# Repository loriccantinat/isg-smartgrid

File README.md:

À propos
========

Ce projet contient les ressources de base pour le projet ISG.

Il contient notamment toutes les informations à propos de la carte MPPTv2
prototype utilisée dans ce projet.

License
=======

À l'exception du dossier datasheets, e projet est partagé sous la licence libre
*Creative Commons Attribution-ShareAlike 4.0 International Public License*.

Pour plus d'informations, voir le fichier `COPYING`.

Les datasheets sont la propriétés des différents fabricants et ont été recopiées
ici pour des raison pratique.

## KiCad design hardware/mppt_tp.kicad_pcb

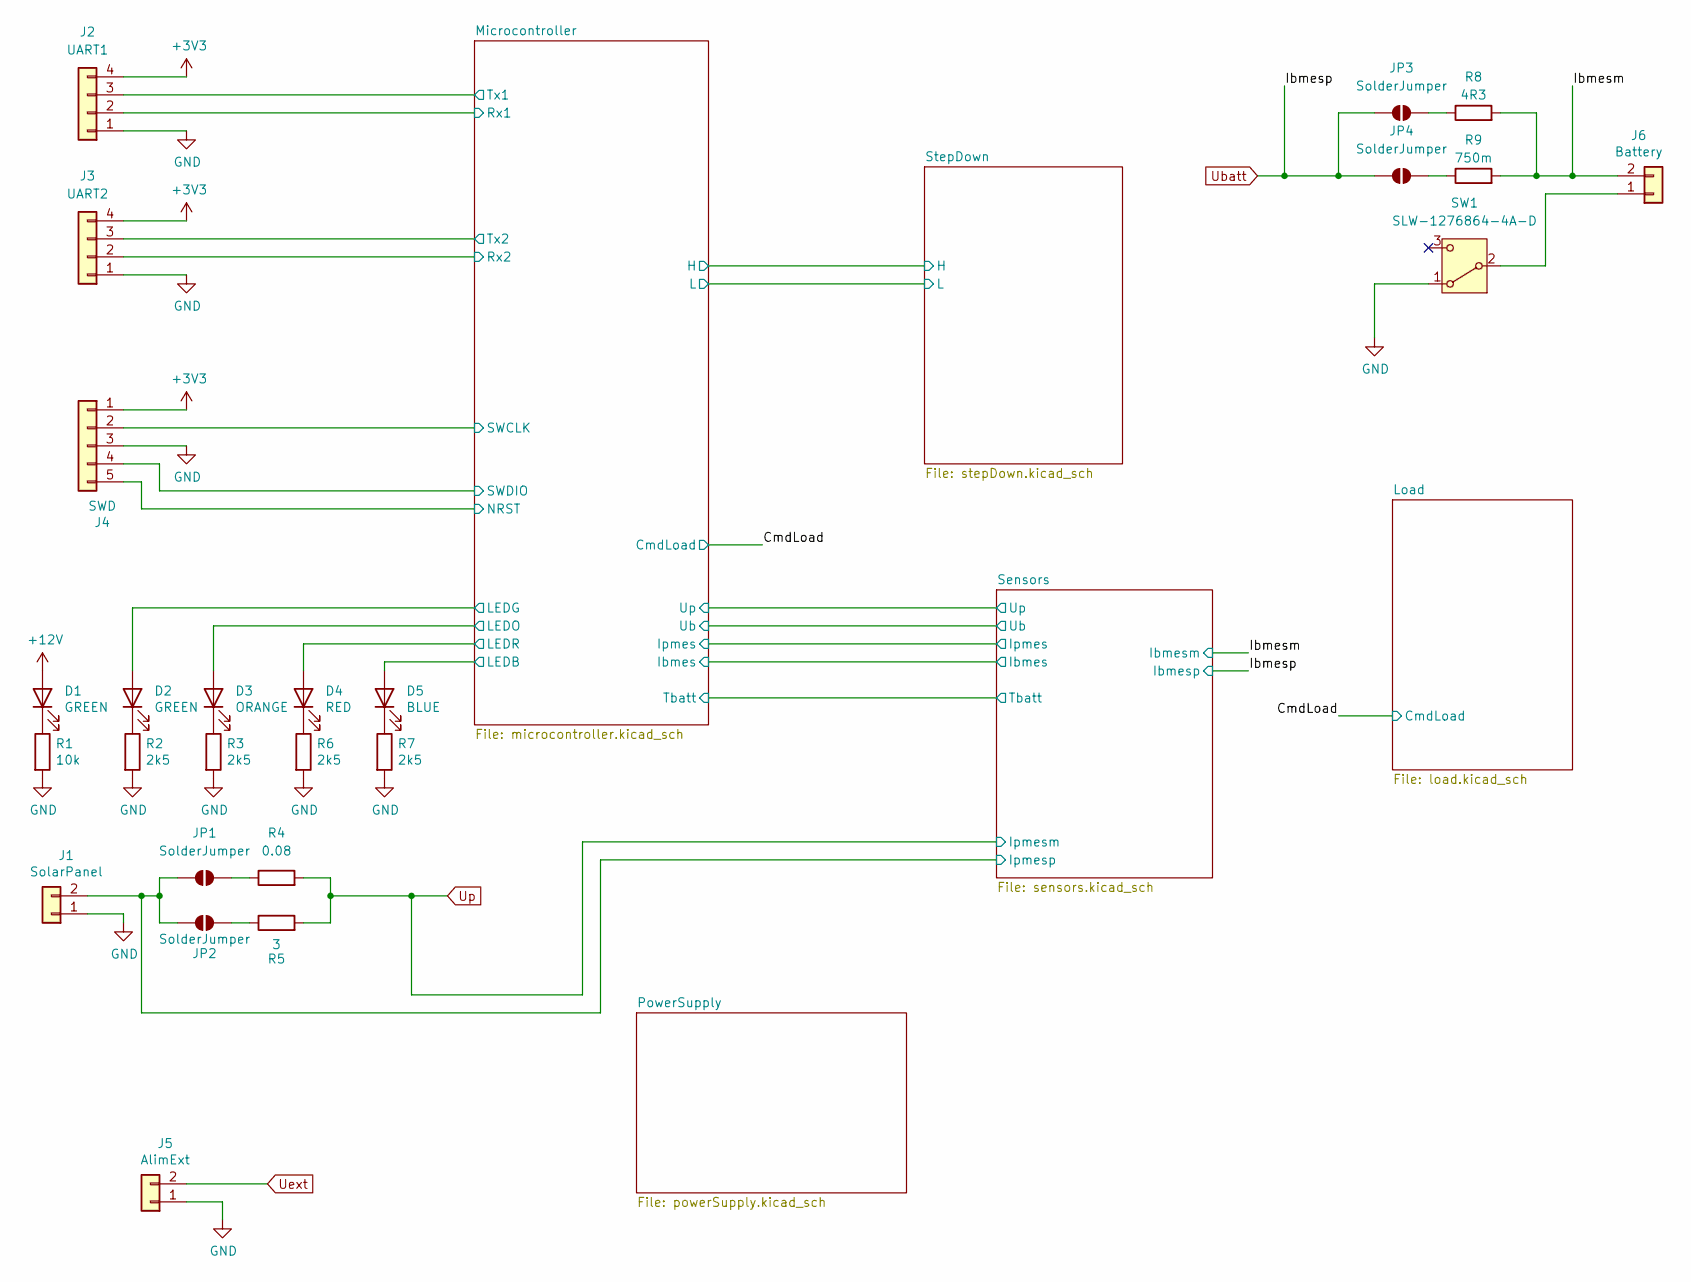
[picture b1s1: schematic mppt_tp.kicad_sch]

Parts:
D1, D2: GREEN; LED_150141_Wurth_HandSolder
D3: ORANGE; LED_150141_Wurth_HandSolder
D4: RED; LED_150141_Wurth_HandSolder
D5: BLUE; LED_150141_Wurth_HandSolder
J1: SolarPanel; Molex_KK-254_AE-6410-02A_1x02_P2.54mm_Vertical
J2: UART1; Molex_KK-254_AE-6410-04A_1x04_P2.54mm_Vertical
J3: UART2; Molex_KK-254_AE-6410-04A_1x04_P2.54mm_Vertical
J4: SWD; Molex_KK-254_AE-6410-05A_1x05_P2.54mm_Vertical
J5: AlimExt; Molex_KK-254_AE-6410-02A_1x02_P2.54mm_Vertical
J6: Battery; Molex_KK-254_AE-6410-02A_1x02_P2.54mm_Vertical
JP1, JP2, JP3, JP4: SolderJumper; SolderJumper-2_P1.3mm_Open_TrianglePad1.0x1.5mm
R1: 10k; R_0805_2012Metric_Pad1.20x1.40mm_HandSolder
R2, R3, R6, R7: 2k5; R_0805_2012Metric_Pad1.20x1.40mm_HandSolder
R4: 0.08; R_1206_3216Metric_HandSolder
R5: 3; R_1206_3216Metric_HandSolder
R8: 4R3; R_1206_3216Metric_HandSolder
R9: 750m; R_1206_3216Metric_HandSolder
SW1: SLW-1276864-4A-D; Switch_SLW-1276864_THT

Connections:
+3V3: J2.4, J3.4, J4.1; also elsewhere on the board
+12V: D1.2 (A); also elsewhere on the board
/Ibmesm: J6.2, R8.2, R9.2; also elsewhere on the board
/Microcontroller/LEDB: D5.2 (A); also elsewhere on the board
/Microcontroller/LEDG: D2.2 (A); also elsewhere on the board
/Microcontroller/LEDO: D3.2 (A); also elsewhere on the board
/Microcontroller/LEDR: D4.2 (A); also elsewhere on the board
/Microcontroller/NRST: J4.5; also elsewhere on the board
/Microcontroller/Rx1: J2.2; also elsewhere on the board
/Microcontroller/Rx2: J3.2; also elsewhere on the board
/Microcontroller/SWCLK: J4.2; also elsewhere on the board
/Microcontroller/SWDIO: J4.4; also elsewhere on the board
/Microcontroller/Tx1: J2.3; also elsewhere on the board
/Microcontroller/Tx2: J3.3; also elsewhere on the board
/Sensors/Ipmesp: J1.2, JP1.1 (A), JP2.1 (A); also elsewhere on the board
GND: J1.1, J2.1, J3.1, J4.3, J5.1, R1.2, R2.2, R3.2, R6.2, R7.2, SW1.1 (A); also elsewhere on the board
unnamed: D1.1 (K), R1.1
unnamed: D2.1 (K), R2.1
unnamed: D3.1 (K), R3.1
unnamed: D4.1 (K), R6.1
unnamed: D5.1 (K), R7.1
unnamed: J6.1, SW1.2 (B)
unnamed: JP1.2 (B), R4.1
unnamed: JP2.2 (B), R5.1
unnamed: JP3.2 (B), R8.1
unnamed: JP4.2 (B), R9.1
Ubatt: JP3.1 (A), JP4.1 (A); also elsewhere on the board
Uext: J5.2; also elsewhere on the board
Up: R4.2, R5.2; also elsewhere on the board

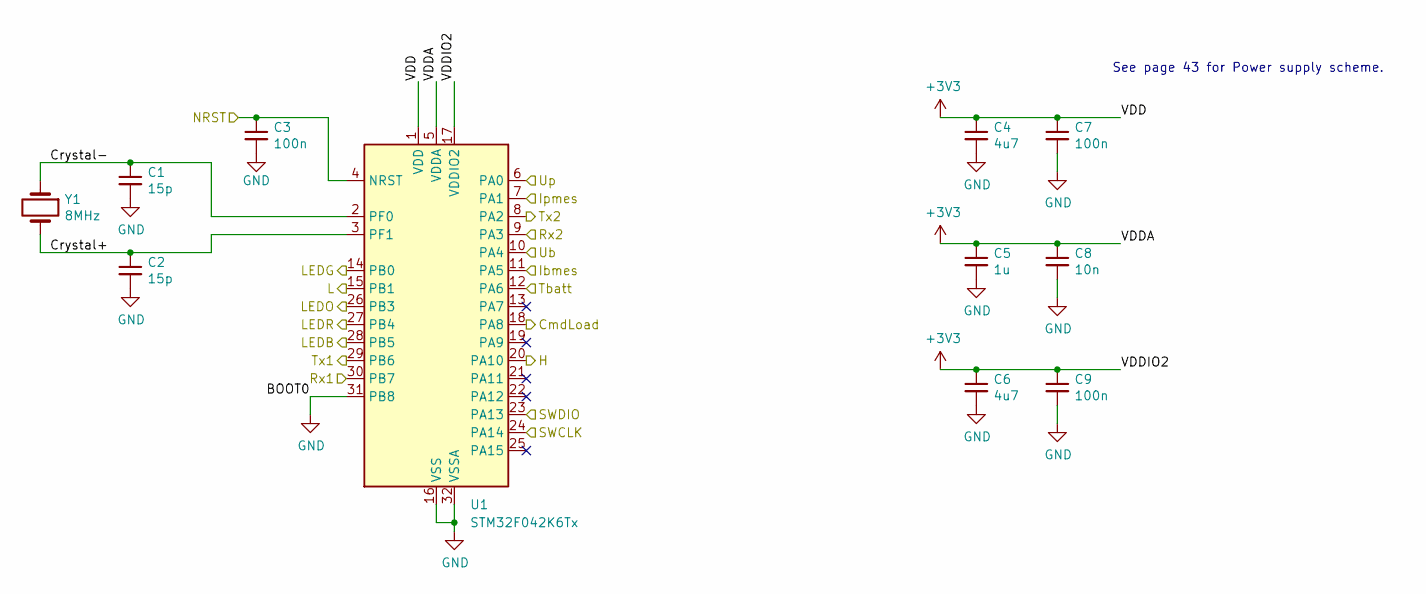
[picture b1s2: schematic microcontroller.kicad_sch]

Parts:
C1, C2: 15p; C_0805_2012Metric_Pad1.18x1.45mm_HandSolder
C3, C7, C9: 100n; C_0805_2012Metric_Pad1.18x1.45mm_HandSolder
C4, C6: 4u7; C_0805_2012Metric_Pad1.18x1.45mm_HandSolder
C5: 1u; C_0805_2012Metric_Pad1.18x1.45mm_HandSolder
C8: 10n; C_0805_2012Metric_Pad1.18x1.45mm_HandSolder
U1: STM32F042K6Tx; LQFP-32_7x7mm_P0.8mm_HandSolder
Y1: 8MHz; Crystal_SMD_ABLS2

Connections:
+3V3: C4.1, C5.1, C6.1, C7.1, C8.1, C9.1, U1.1 (VDD), U1.5 (VDDA), U1.17 (VDDIO2); also elsewhere on the board
/CmdLoad: U1.18 (PA8); also elsewhere on the board
/Microcontroller/Crystal+: C2.1, U1.3 (PF1), Y1.2
/Microcontroller/Crystal-: C1.1, U1.2 (PF0), Y1.1
/Microcontroller/H: U1.20 (PA10); also elsewhere on the board
/Microcontroller/Ibmes: U1.11 (PA5); also elsewhere on the board
/Microcontroller/Ipmes: U1.7 (PA1); also elsewhere on the board
/Microcontroller/L: U1.15 (PB1); also elsewhere on the board
/Microcontroller/LEDB: U1.28 (PB5); also elsewhere on the board
/Microcontroller/LEDG: U1.14 (PB0); also elsewhere on the board
/Microcontroller/LEDO: U1.26 (PB3); also elsewhere on the board
/Microcontroller/LEDR: U1.27 (PB4); also elsewhere on the board
/Microcontroller/NRST: C3.1, U1.4 (NRST); also elsewhere on the board
/Microcontroller/Rx1: U1.30 (PB7); also elsewhere on the board
/Microcontroller/Rx2: U1.9 (PA3); also elsewhere on the board
/Microcontroller/SWCLK: U1.24 (PA14); also elsewhere on the board
/Microcontroller/SWDIO: U1.23 (PA13); also elsewhere on the board
/Microcontroller/Tbatt: U1.12 (PA6); also elsewhere on the board
/Microcontroller/Tx1: U1.29 (PB6); also elsewhere on the board
/Microcontroller/Tx2: U1.8 (PA2); also elsewhere on the board
/Microcontroller/Ub: U1.10 (PA4); also elsewhere on the board
/Microcontroller/Up: U1.6 (PA0); also elsewhere on the board
GND: C1.2, C2.2, C3.2, C4.2, C5.2, C6.2, C7.2, C8.2, C9.2, U1.16 (VSS), U1.31 (PB8), U1.32 (VSSA); also elsewhere on the board

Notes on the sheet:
See page 43 for Power supply scheme.

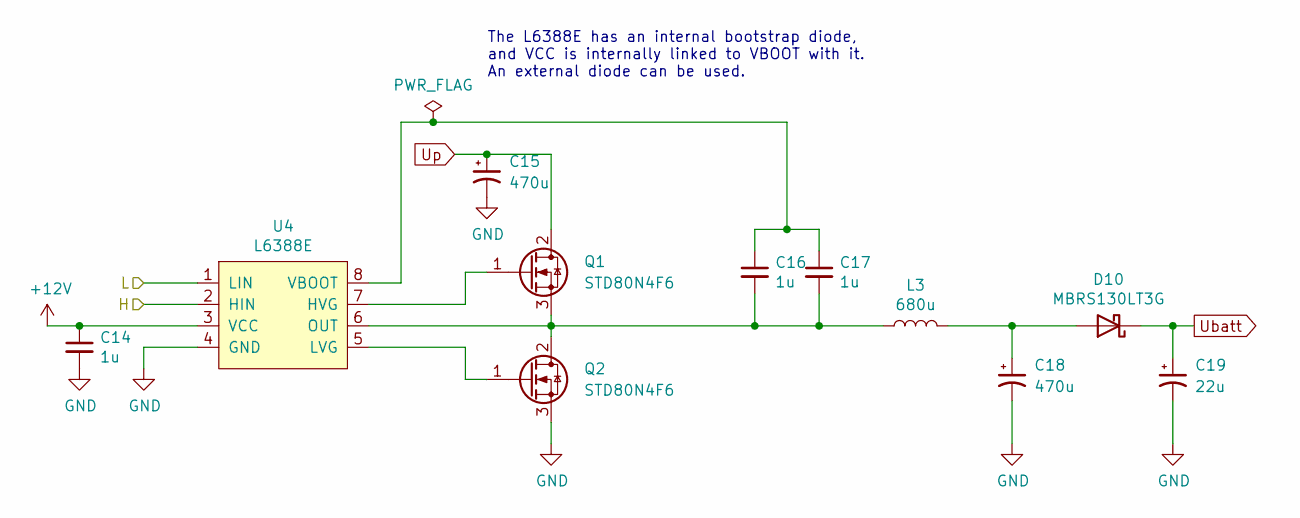
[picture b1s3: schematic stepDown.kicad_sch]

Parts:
C14, C16, C17: 1u; C_0805_2012Metric_Pad1.18x1.45mm_HandSolder
C15, C18: 470u; CP_Elec_16x16.5_Panasonic
C19: 22u; CP_Elec_6.3x5.8_Panasonic_HandSolder
D10: MBRS130LT3G; Diode_SMD_MBRS130LT3G_HandSolder
L3: 680u; Inductor_SMD_Coilcraft_MSS1278H_HandSolder
Q1, Q2: STD80N4F6; TO-252-2_HandSolder
U4: L6388E; SO-8_3.9x4.9mm_P1.27mm_HandSolder

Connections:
+12V: C14.1, U4.3 (VCC); also elsewhere on the board
/Microcontroller/H: U4.2 (HIN); also elsewhere on the board
/Microcontroller/L: U4.1 (LIN); also elsewhere on the board
GND: C14.2, C15.2, C18.2, C19.2, Q2.3 (S), U4.4 (GND); also elsewhere on the board
unnamed: C18.1, D10.2 (A), L3.2
unnamed: Q1.1 (G), U4.7 (HVG)
unnamed: C16.2, C17.2, L3.1, Q1.3 (S), Q2.2 (D), U4.6 (OUT)
unnamed: Q2.1 (G), U4.5 (LVG)
unnamed: C16.1, C17.1, U4.8 (VBOOT)
Ubatt: C19.1, D10.1 (K); also elsewhere on the board
Up: C15.1, Q1.2 (D); also elsewhere on the board

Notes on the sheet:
The L6388E has an internal bootstrap diode, and VCC is internally linked to VBOOT with it. An external diode can be used.

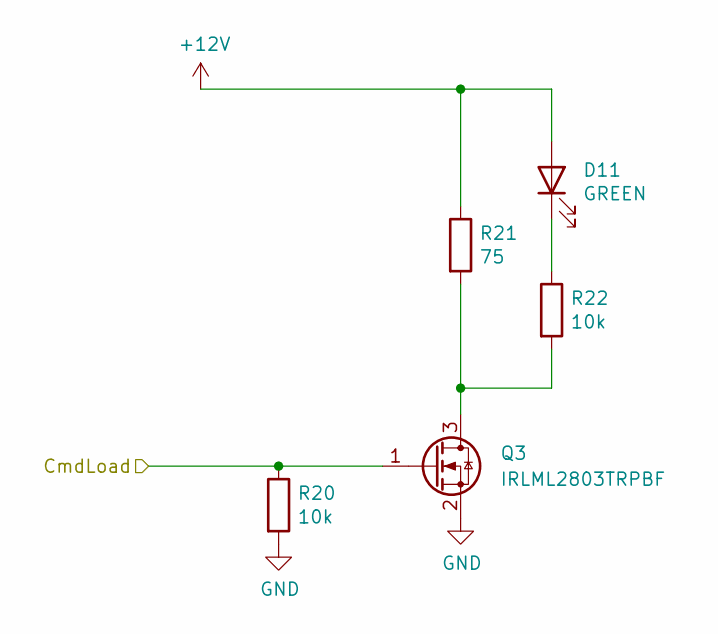
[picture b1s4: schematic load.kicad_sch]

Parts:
D11: GREEN; LED_150141_Wurth_HandSolder
Q3: IRLML2803TRPBF; SOT-23_Handsoldering
R20, R22: 10k; R_0805_2012Metric_Pad1.20x1.40mm_HandSolder
R21: 75; Resistor_SMD_1225Large_HandSolder

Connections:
+12V: D11.2 (A), R21.1; also elsewhere on the board
/CmdLoad: Q3.1 (G), R20.1; also elsewhere on the board
GND: Q3.2 (S), R20.2; also elsewhere on the board
unnamed: D11.1 (K), R22.1
unnamed: Q3.3 (D), R21.2, R22.2

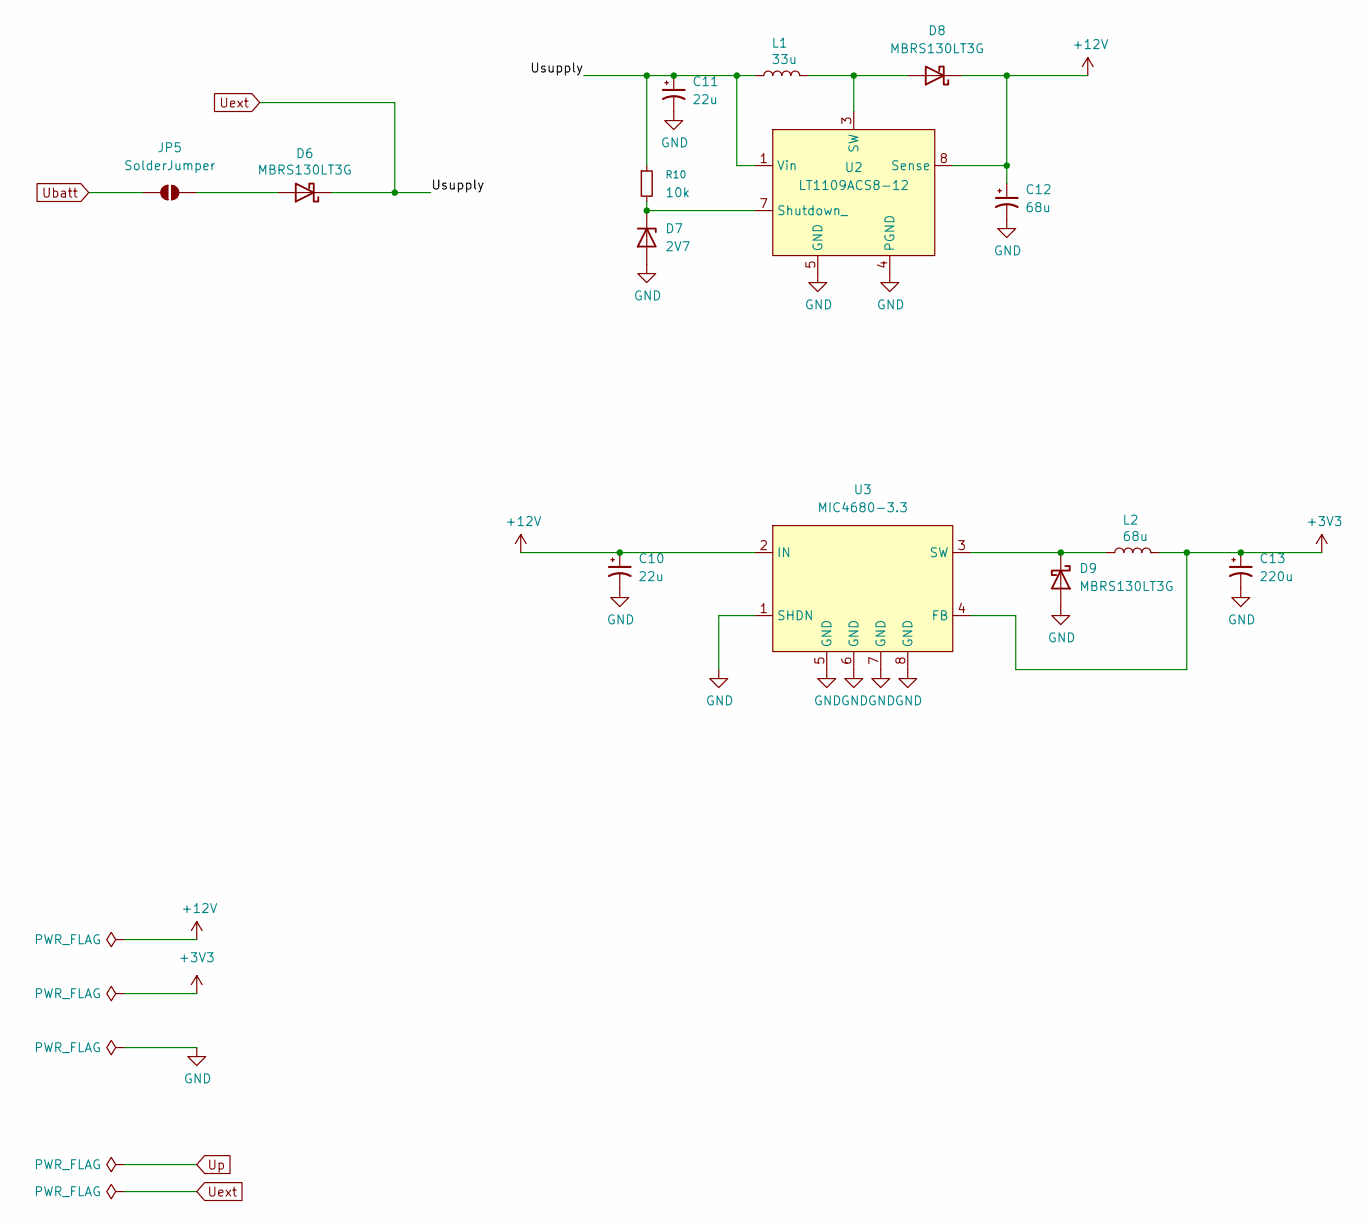
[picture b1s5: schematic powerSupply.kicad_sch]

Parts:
C10, C11: 22u; CP_Elec_6.3x5.8_Panasonic_HandSolder
C12: 68u; CP_Elec_8x10.5_Panasonic_HandSolder
C13: 220u; CP_Elec_10x10.5_Panasonic_HandSolder
D6, D8, D9: MBRS130LT3G; Diode_SMD_MBRS130LT3G_HandSolder
D7: 2V7; Diode_Zener_PLC6V8C-HG3_A_H
JP5: SolderJumper; SolderJumper-2_P1.3mm_Open_TrianglePad1.0x1.5mm
L1: 33u; Inductor_SMD_Coilcraft_LPS6235_HandSolder
L2: 68u; Inductor_SMD_Coilcraft_LPS6235_HandSolder
R10: 10k; R_0805_2012Metric_Pad1.20x1.40mm_HandSolder
U2: LT1109ACS8-12; SOIC-8_3.9x4.9mm_P1.27mm_HandSolder
U3: MIC4680-3.3; SOIC-8_3.9x4.9mm_P1.27mm_HandSolder

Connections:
+3V3: C13.1, L2.2, U3.4 (FB); also elsewhere on the board
+12V: C10.1, C12.1, D8.1 (K), U2.8 (Sense), U3.2 (IN); also elsewhere on the board
GND: C10.2, C11.2, C12.2, C13.2, D7.2 (A), D9.2 (A), U2.4 (PGND), U2.5 (GND), U3.1 (SHDN), U3.5 (GND), U3.6 (GND), U3.7 (GND), U3.8 (GND); also elsewhere on the board
unnamed: D6.2 (A), JP5.2 (B)
unnamed: D7.1 (K), R10.2, U2.7 (Shutdown_)
unnamed: D8.2 (A), L1.2, U2.3 (SW)
unnamed: D9.1 (K), L2.1, U3.3 (SW)
Ubatt: JP5.1 (A); also elsewhere on the board
Uext: C11.1, D6.1 (K), L1.1, R10.1, U2.1 (Vin); also elsewhere on the board

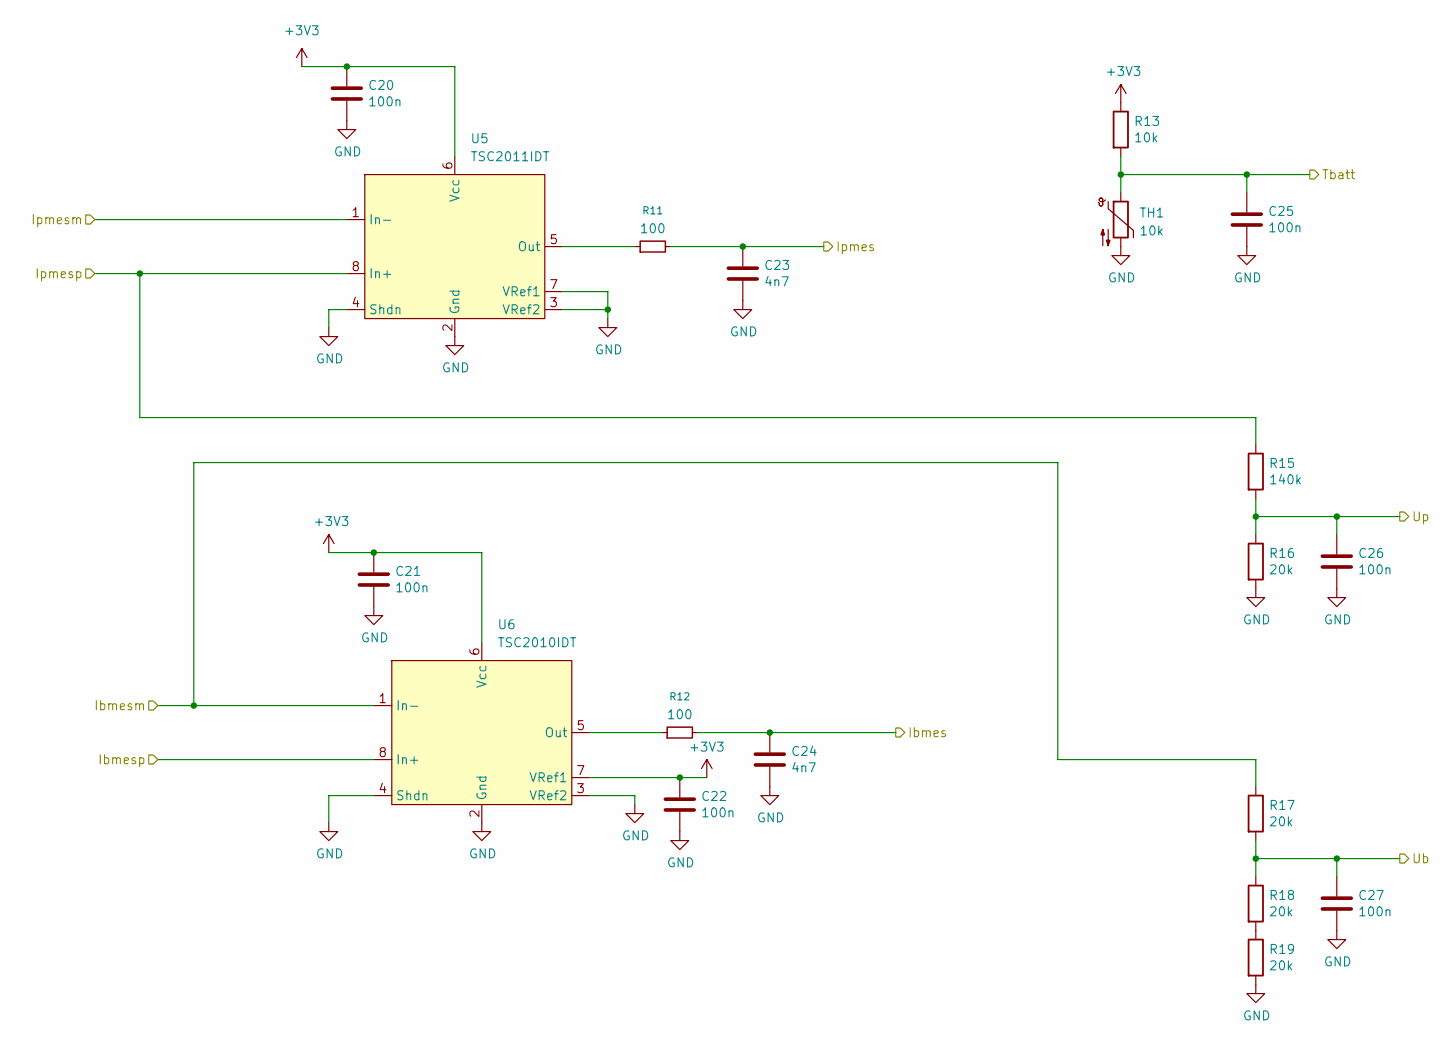
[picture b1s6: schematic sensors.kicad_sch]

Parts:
C20, C21, C22, C25, C26, C27: 100n; C_0805_2012Metric_Pad1.18x1.45mm_HandSolder
C23, C24: 4n7; C_0805_2012Metric_Pad1.18x1.45mm_HandSolder
R11, R12: 100; R_0805_2012Metric_Pad1.20x1.40mm_HandSolder
R13: 10k; R_0805_2012Metric_Pad1.20x1.40mm_HandSolder
R15: 140k; R_0805_2012Metric_Pad1.20x1.40mm_HandSolder
R16, R17, R18, R19: 20k; R_0805_2012Metric_Pad1.20x1.40mm_HandSolder
TH1: 10k; R_0805_2012Metric_Pad1.20x1.40mm_HandSolder
U5: TSC2011IDT; SO-8_3.9x4.9mm_P1.27mm_HandSolder
U6: TSC2010IDT; SO-8_3.9x4.9mm_P1.27mm_HandSolder

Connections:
+3V3: C20.1, C21.1, C22.1, R13.1, U5.6 (Vcc), U6.6 (Vcc), U6.7 (VRef1); also elsewhere on the board
/Ibmesm: R17.1, U6.1 (In-); also elsewhere on the board
/Microcontroller/Ibmes: C24.1, R12.2; also elsewhere on the board
/Microcontroller/Ipmes: C23.1, R11.2; also elsewhere on the board
/Microcontroller/Tbatt: C25.1, R13.2, TH1.1; also elsewhere on the board
/Microcontroller/Ub: C27.1, R17.2, R18.1; also elsewhere on the board
/Microcontroller/Up: C26.1, R15.2, R16.1; also elsewhere on the board
/Sensors/Ipmesp: R15.1, U5.8 (In+); also elsewhere on the board
GND: C20.2, C21.2, C22.2, C23.2, C24.2, C25.2, C26.2, C27.2, R16.2, R19.2, TH1.2, U5.2 (Gnd), U5.3 (VRef2), U5.4 (Shdn), U5.7 (VRef1), U6.2 (Gnd), U6.3 (VRef2), U6.4 (Shdn); also elsewhere on the board
unnamed: R18.2, R19.1
unnamed: R11.1, U5.5 (Out)
unnamed: R12.1, U6.5 (Out)
Ubatt: U6.8 (In+); also elsewhere on the board
Up: U5.1 (In-); also elsewhere on the board

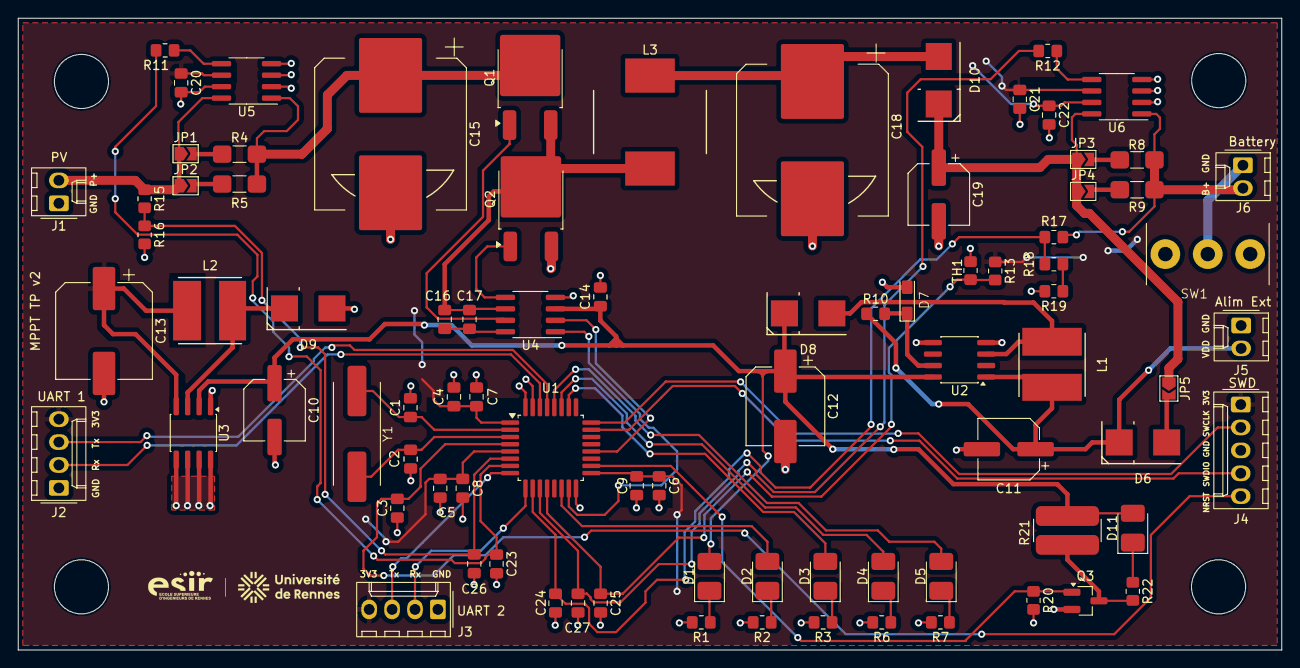
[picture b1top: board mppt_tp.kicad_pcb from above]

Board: 2 copper layers, 140.0 x 70.0 mm, 85 parts (0 on the bottom side), 53 nets.
